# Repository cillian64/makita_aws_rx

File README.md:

Really simple receiver for the Makita AWS bluetooth wireless dust extractor
system.

Runs on Micropython on a Raspberry Pi Pico W.

Doesn't actually support pairing at all, just listens to any Makita AWS
transmitter in range.

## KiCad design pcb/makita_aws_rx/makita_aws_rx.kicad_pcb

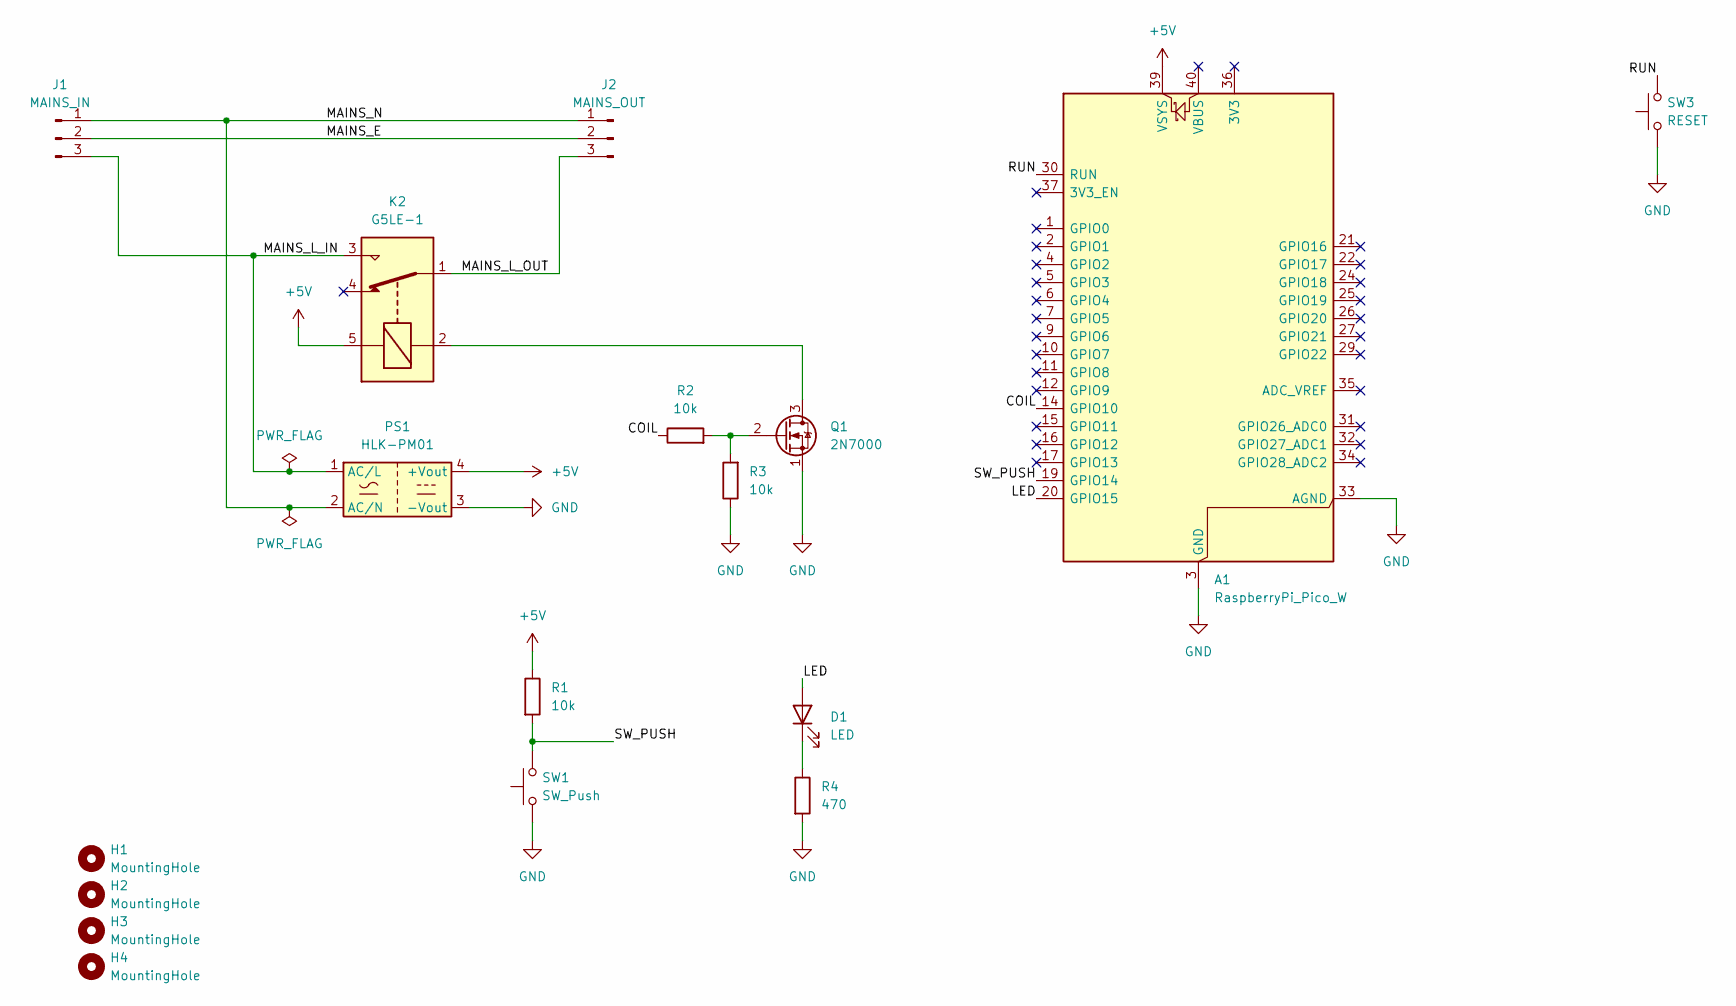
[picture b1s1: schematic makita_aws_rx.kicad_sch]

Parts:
A1: RaspberryPi_Pico_W; RaspberryPi_Pico_Common_THT
D1: LED; SolderWire-0.5sqmm_1x02_P4.6mm_D0.9mm_OD2.1mm
H1, H2, H3, H4: MountingHole; MountingHole_3.5mm
J1: MAINS_IN; TerminalBlock_MetzConnect_Type011_RT05503HBLC_1x03_P5.00mm_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
J2: MAINS_OUT; TerminalBlock_MetzConnect_Type011_RT05503HBLC_1x03_P5.00mm_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
K2: G5LE-1; Relay_SPDT_Omron-G5LE-1
PS1: HLK-PM01; Converter_ACDC_Hi-Link_HLK-PMxx
Q1: 2N7000; TO-92_Inline
R1, R2, R3: 10k; R_Axial_DIN0207_L6.3mm_D2.5mm_P7.62mm_Horizontal
R4: 470; R_Axial_DIN0207_L6.3mm_D2.5mm_P7.62mm_Horizontal
SW1: SW_Push; SolderWire-0.5sqmm_1x02_P4.6mm_D0.9mm_OD2.1mm
SW3: RESET; SW_PUSH_6mm_H4.3mm

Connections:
+5V: A1.39 (VSYS), K2.5, PS1.4 (+Vout), R1.1
/COIL: A1.14 (GPIO10), R2.1
/LED: A1.20 (GPIO15), D1.2 (A)
/MAINS_E: J1.2, J2.2
/MAINS_L_IN: J1.3, K2.3, PS1.1 (AC/L)
/MAINS_L_OUT: J2.3, K2.1
/MAINS_N: J1.1, J2.1, PS1.2 (AC/N)
/RUN: A1.30 (RUN), SW3.2
/SW_PUSH: A1.19 (GPIO14), R1.2, SW1.2
GND: A1.3 (GND), A1.8 (GND), A1.13 (GND), A1.18 (GND), A1.23 (GND), A1.28 (GND), A1.33 (AGND), A1.38 (GND), PS1.3 (-Vout), Q1.1 (S), R3.1, R4.2, SW1.1, SW3.1
unnamed: D1.1 (K), R4.1
unnamed: K2.2, Q1.3 (D)
unnamed: Q1.2 (G), R2.2, R3.2

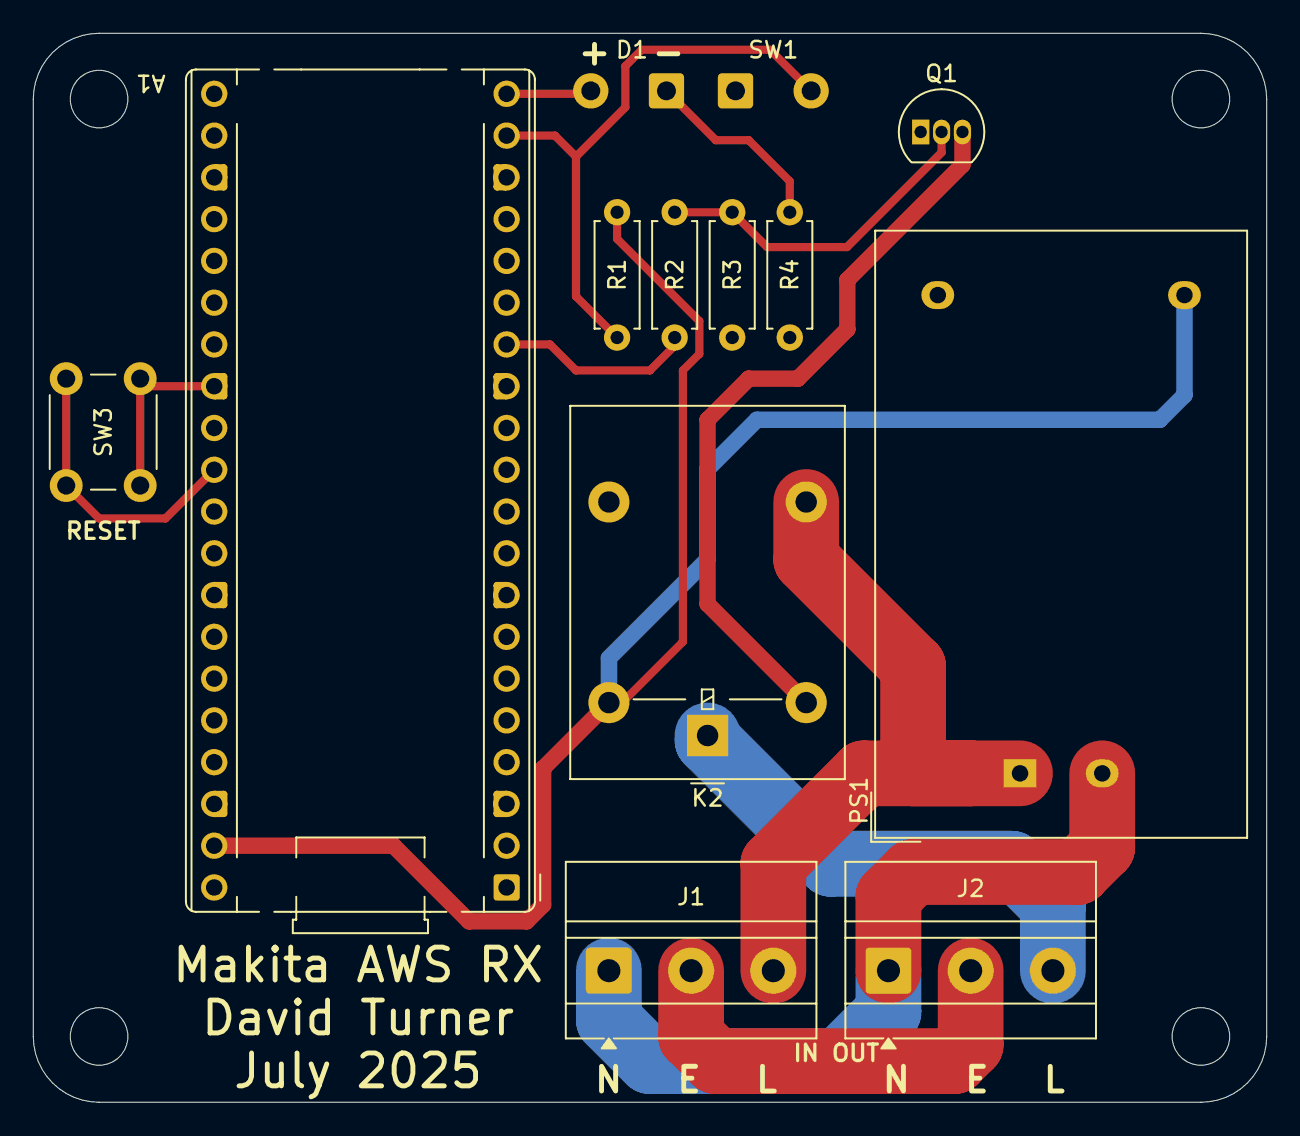
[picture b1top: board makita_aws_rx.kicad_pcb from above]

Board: 2 copper layers, 75.0 x 65.0 mm, 17 parts (0 on the bottom side), 13 nets.

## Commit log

2025-07-18 Basic working AWS receiver code
2025-07-18 Schematic/PCB WIP
2025-07-18 PCB nearly done
2025-07-19 Final PCB
2025-07-19 Gerbers
2025-08-03 Basically finished code
2025-08-03 Fix bug with override sw and LED
